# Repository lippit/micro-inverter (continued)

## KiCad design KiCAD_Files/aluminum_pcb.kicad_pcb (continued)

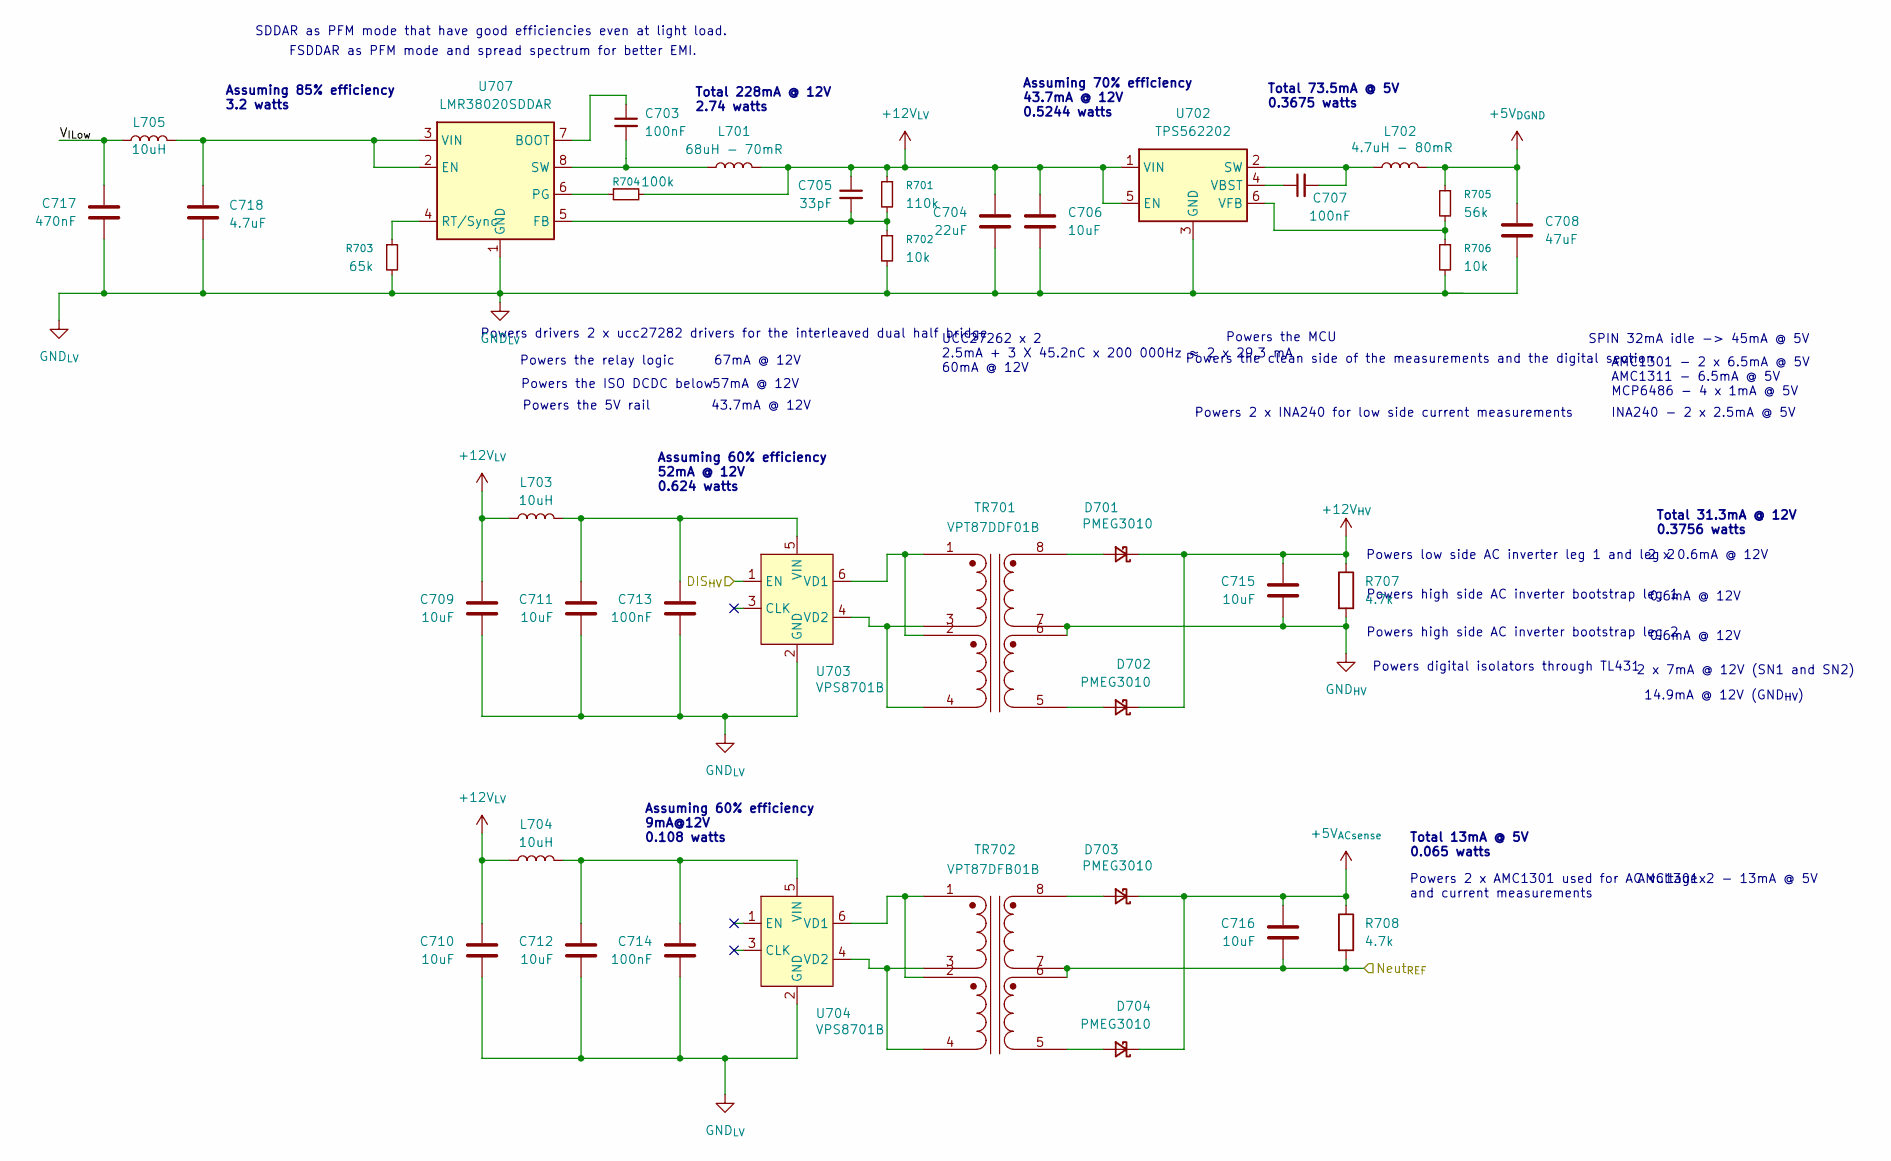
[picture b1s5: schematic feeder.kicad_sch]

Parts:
C703, C707: 100nF; C_0805_2012Metric
C704: 22uF; C_1210_3225Metric
C705: 33pF; C_0805_2012Metric
C706: 10uF; C_0805_2012Metric
C708: 47uF; C_1206_3216Metric
C709, C710, C711, C712, C715, C716: 10uF; C_0805_2012Metric; LCSC C440198
C713, C714: 100nF; C_0603_1608Metric; LCSC C14663
C717: 470nF; C_0805_2012Metric; Voltage_Rating 100V
C718: 4.7uF; C_1210_3225Metric; Voltage_Rating 100V
D701, D702, D703, D704: PMEG3010; D_SOD-323F; LCSC C255586
L701: 68uH - 70mR; L_12x12mm_H6mm; LCSC C7587712
L702: 4.7uH - 80mR; L_Cenker_CKCS4020; LCSC C3002596
L703, L704: 10uH; L_0805_2012Metric
L705: 10uH; L_1210_3225Metric
R701: 110k; R_0805_2012Metric
R702, R706: 10k; R_0805_2012Metric
R703: 65k; R_0805_2012Metric
R704: 100k; R_0805_2012Metric
R705: 56k; R_0805_2012Metric
R707, R708: 4.7k; R_0603_1608Metric; LCSC C23162
TR701: VPT87DDF01B; VPT87BB-01B; LCSC C2846916
TR702: VPT87DFB01B; VPT87BB-01B; LCSC C2846915
U702: TPS562202; SOT-563; LCSC C2877547
U703, U704: VPS8701B; SOT-23-6; LCSC C5189123
U707: LMR38020SDDAR; Texas_HSOP-8-1EP_3.9x4.9mm_P1.27mm_ThermalVias; LCSC C3192337

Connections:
+5V_{ACsense}: C716.1, D703.1 (K), D704.1 (K), R708.1; also elsewhere on the board
+5V_{DGND}: C708.1, L702.2, R705.1; also elsewhere on the board
+12V_{HV}: C715.1, D701.1 (K), D702.1 (K), R707.1; also elsewhere on the board
/Feeder/DIS_{HV}: U703.1 (EN); also elsewhere on the board
/Feeder/Neut_{REF}: C716.2, R708.2, TR702.6 (SB), TR702.7 (SA); also elsewhere on the board
/Feeder/V_{ILow}: C717.1, L705.1
GND_{HV}: C715.2, R707.2, TR701.6 (SB), TR701.7 (SA); also elsewhere on the board
unnamed: D701.2 (A), TR701.8 (SB)
unnamed: D702.2 (A), TR701.5 (SA)
unnamed: D703.2 (A), TR702.8 (SB)
unnamed: D704.2 (A), TR702.5 (SA)
unnamed: C707.2, L702.1, U702.2 (SW)
unnamed: C707.1, U702.4 (VBST)
unnamed: R705.2, R706.1, U702.6 (VFB)
unnamed: TR701.1 (AA), TR701.2 (AA), U703.6 (VD1)
unnamed: TR701.3 (AB), TR701.4 (AB), U703.4 (VD2)
unnamed: C711.1, C713.1, L703.2, U703.5 (VIN)
unnamed: TR702.1 (AA), TR702.2 (AA), U704.6 (VD1)
unnamed: TR702.3 (AB), TR702.4 (AB), U704.4 (VD2)
unnamed: C712.1, C714.1, L704.2, U704.5 (VIN)
unnamed: C703.1, U707.7 (BOOT)
unnamed: C718.1, L705.2, U707.2 (EN), U707.3 (VIN)
unnamed: C705.2, R701.2, R702.1, U707.5 (FB)
unnamed: R704.1, U707.6 (PG)
unnamed: R703.1, U707.4 (RT/Sync)
unnamed: C703.2, L701.1, U707.8 (SW)

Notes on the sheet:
Powers the 5V rail
Powers digital isolators through TL431
Total 73.5mA @ 5V 0.3675 watts
Assuming 70% efficiency 43.7mA @ 12V 0.5244 watts
AMC1301x2 - 13mA @ 5V
INA240 - 2 x 2.5mA @ 5V
Powers the clean side of the measurements and the digital section
Powers 2 x AMC1301 used for AC voltage and current measurements
Powers high side AC inverter bootstrap leg 1
Total 13mA @ 5V 0.065 watts
Assuming 60% efficiency 9mA@12V 0.108 watts
Assuming 60% efficiency 52mA @ 12V 0.624 watts
0.6mA @ 12V
Powers 2 x INA240 for low side current measurements
Powers low side AC inverter leg 1 and leg 2
Powers the ISO DCDC below
SPIN 32mA idle -> 45mA @ 5V
14.9mA @ 12V (GND_{HV})
Powers drivers 2 x ucc27282 drivers for the interleaved dual half bridge
57mA @ 12V
UCC27262 x 2 2.5mA + 3 X 45.2nC x 200 000Hz ≈ 2 x 29.3 mA 60mA @ 12V
FSDDAR as PFM mode and spread spectrum for better EMI.
43.7mA @ 12V
2 x 0.6mA @ 12V
AMC1301 - 2 x 6.5mA @ 5V AMC1311 - 6.5mA @ 5V MCP6486 - 4 x 1mA @ 5V
2 x 7mA @ 12V (SN1 and SN2)
Total 228mA @ 12V 2.74 watts
Powers the MCU
Assuming 85% efficiency 3.2 watts
Total 31.3mA @ 12V 0.3756 watts
Powers the relay logic
67mA @ 12V
Powers high side AC inverter bootstrap leg 2
SDDAR as PFM mode that have good efficiencies even at light load.

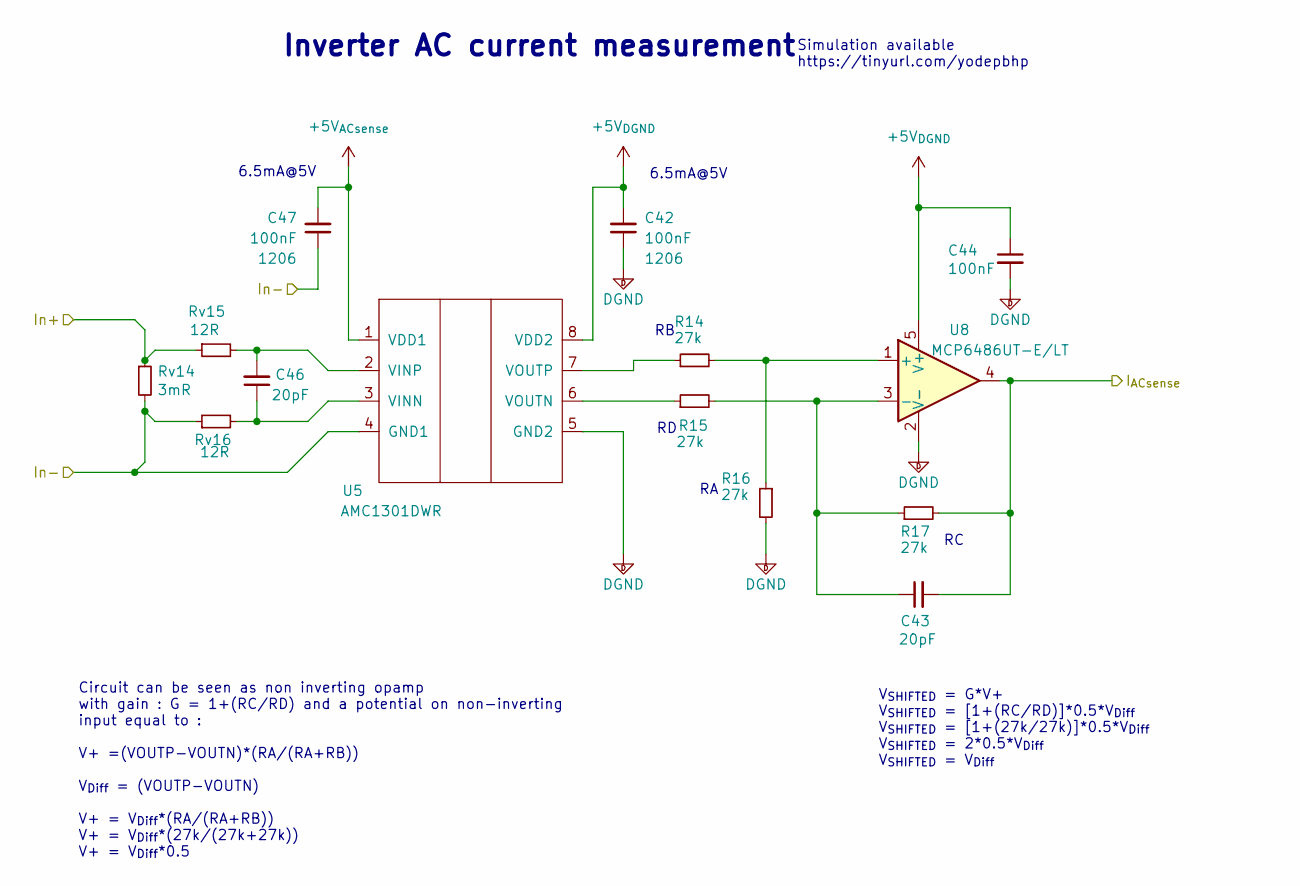
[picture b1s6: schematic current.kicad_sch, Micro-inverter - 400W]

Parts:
C42, C47: 100nF; C_1206_3216Metric; Voltage 50V; LCSC C5449000
C43, C46: 20pF; C_0805_2012Metric; Voltage 50V
C44: 100nF; C_0805_2012Metric; Voltage 50V; LCSC C5449000
R14, R15, R16, R17: 27k; R_0805_2012Metric
Rv14: 3mR; R_2512_6332Metric
Rv15, Rv16: 12R; R_0805_2012Metric
U5: AMC1301DWR; SOIC-8_7.5x5.85mm_P1.27mm; LCSC C190273
U8: MCP6486UT-E/LT; SOT-353_SC-70-5_Handsoldering; LCSC C5224800

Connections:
+5V_{ACsense}: C47.2, U5.1 (VDD1); also elsewhere on the board
+5V_{DGND}: C42.2, C44.1, U5.8 (VDD2), U8.5 (V+); also elsewhere on the board
/Feeder/Neut_{REF}: C47.1, Rv14.2, Rv16.1, U5.4 (GND1); also elsewhere on the board
/Microcontroller/I_{AC}: C43.2, R17.2, U8.4; also elsewhere on the board
/Power/AC Current sense/In+: Rv14.1, Rv15.1; also elsewhere on the board
unnamed: C46.1, Rv16.2, U5.3 (VINN)
unnamed: C46.2, Rv15.2, U5.2 (VINP)
unnamed: R15.1, U5.6 (VOUTN)
unnamed: R14.1, U5.7 (VOUTP)
unnamed: R14.2, R16.1, U8.1 (+)
unnamed: C43.1, R15.2, R17.1, U8.3 (-)

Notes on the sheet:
Simulation available https://tinyurl.com/yodepbhp
6.5mA@5V
Circuit can be seen as non inverting opamp with gain : G = 1+(RC/RD) and a potential on non-inverting input equal to : V+ =(VOUTP-VOUTN)*(RA/(RA+RB)) V_{Diff} = (VOUTP-VOUTN) V+ = V_{Diff}*(RA/(RA+RB)) V+ = V_{Diff}*(27k/(27k+27k)) V+ = V_{Diff}*0.5
V_{SHIFTED} = G*V+ V_{SHIFTED} = [1+(RC/RD)]*0.5*V_{Diff} V_{SHIFTED} = [1+(27k/27k)]*0.5*V_{Diff} V_{SHIFTED} = 2*0.5*V_{Diff} V_{SHIFTED} = V_{Diff}
Inverter AC current measurement

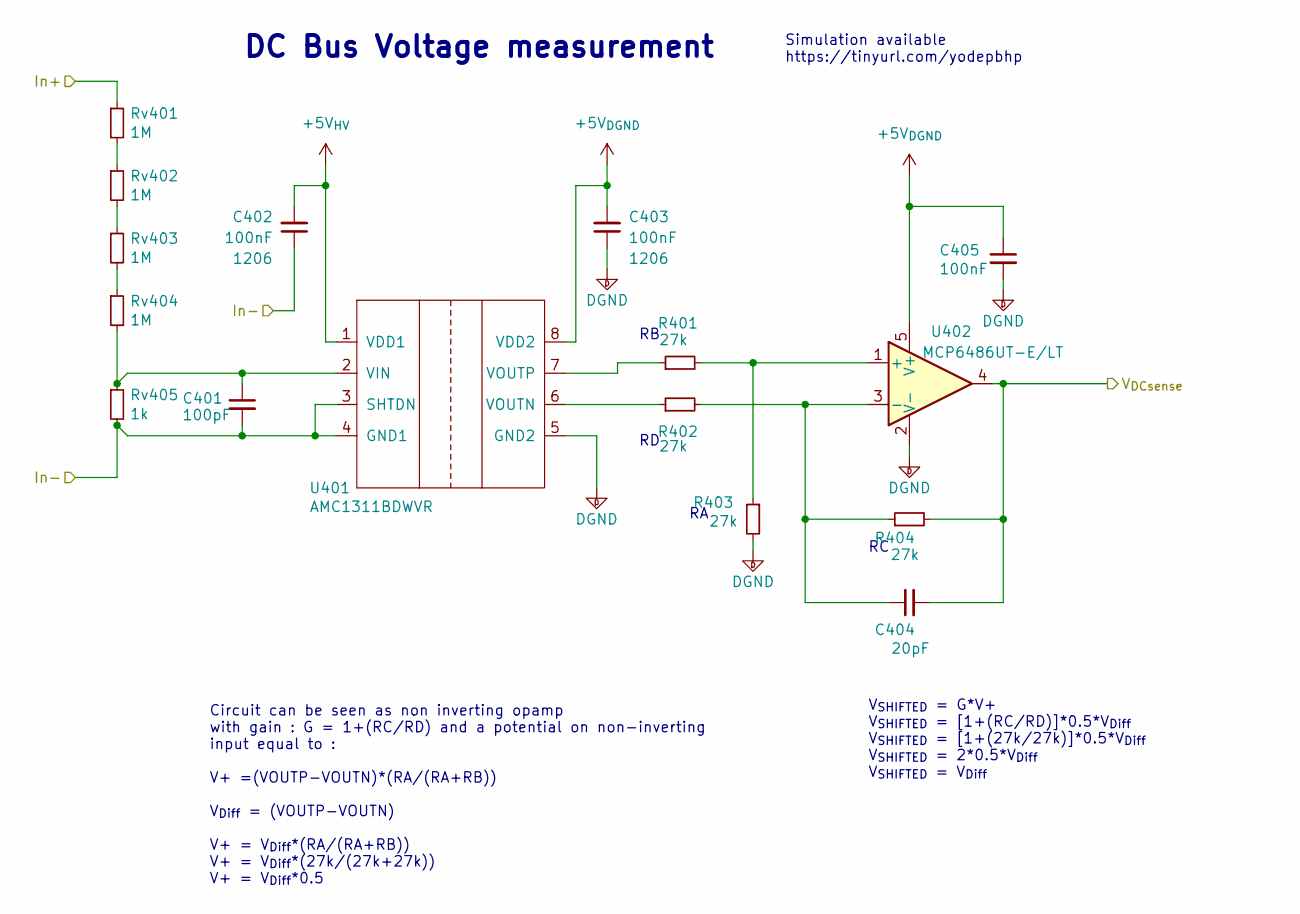
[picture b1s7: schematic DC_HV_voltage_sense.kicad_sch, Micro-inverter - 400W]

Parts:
C401: 100pF; C_0805_2012Metric; Voltage 50V
C402, C403: 100nF; C_1206_3216Metric; Voltage 50V; LCSC C5449000
C404: 20pF; C_0805_2012Metric; Voltage 50V
C405: 100nF; C_0805_2012Metric; Voltage 50V; LCSC C5449000
R401, R402, R403, R404: 27k; R_0805_2012Metric
Rv401, Rv402, Rv403, Rv404: 1M; R_0805_2012Metric
Rv405: 1k; R_0805_2012Metric
U401: AMC1311BDWVR; SOIC-8_7.5x5.85mm_P1.27mm; LCSC C783598
U402: MCP6486UT-E/LT; SOT-353_SC-70-5_Handsoldering; LCSC C5224800

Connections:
+5V_{DGND}: C403.2, C405.1, U401.8 (VDD2), U402.5 (V+); also elsewhere on the board
+5V_{HV}: C402.2, U401.1 (VDD1); also elsewhere on the board
/Microcontroller/V_{DCBus}: C404.2, R404.2, U402.4; also elsewhere on the board
/Power/HV_{BUS}: Rv401.1; also elsewhere on the board
GND_{HV}: C401.2, C402.1, Rv405.2, U401.3 (SHTDN), U401.4 (GND1); also elsewhere on the board
unnamed: Rv401.2, Rv402.1
unnamed: Rv402.2, Rv403.1
unnamed: Rv403.2, Rv404.1
unnamed: C401.1, Rv404.2, Rv405.1, U401.2 (VIN)
unnamed: R402.1, U401.6 (VOUTN)
unnamed: R401.1, U401.7 (VOUTP)
unnamed: R401.2, R403.1, U402.1 (+)
unnamed: C404.1, R402.2, R404.1, U402.3 (-)

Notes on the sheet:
Circuit can be seen as non inverting opamp with gain : G = 1+(RC/RD) and a potential on non-inverting input equal to : V+ =(VOUTP-VOUTN)*(RA/(RA+RB)) V_{Diff} = (VOUTP-VOUTN) V+ = V_{Diff}*(RA/(RA+RB)) V+ = V_{Diff}*(27k/(27k+27k)) V+ = V_{Diff}*0.5
DC Bus Voltage measurement
V_{SHIFTED} = G*V+ V_{SHIFTED} = [1+(RC/RD)]*0.5*V_{Diff} V_{SHIFTED} = [1+(27k/27k)]*0.5*V_{Diff} V_{SHIFTED} = 2*0.5*V_{Diff} V_{SHIFTED} = V_{Diff}
Simulation available https://tinyurl.com/yodepbhp

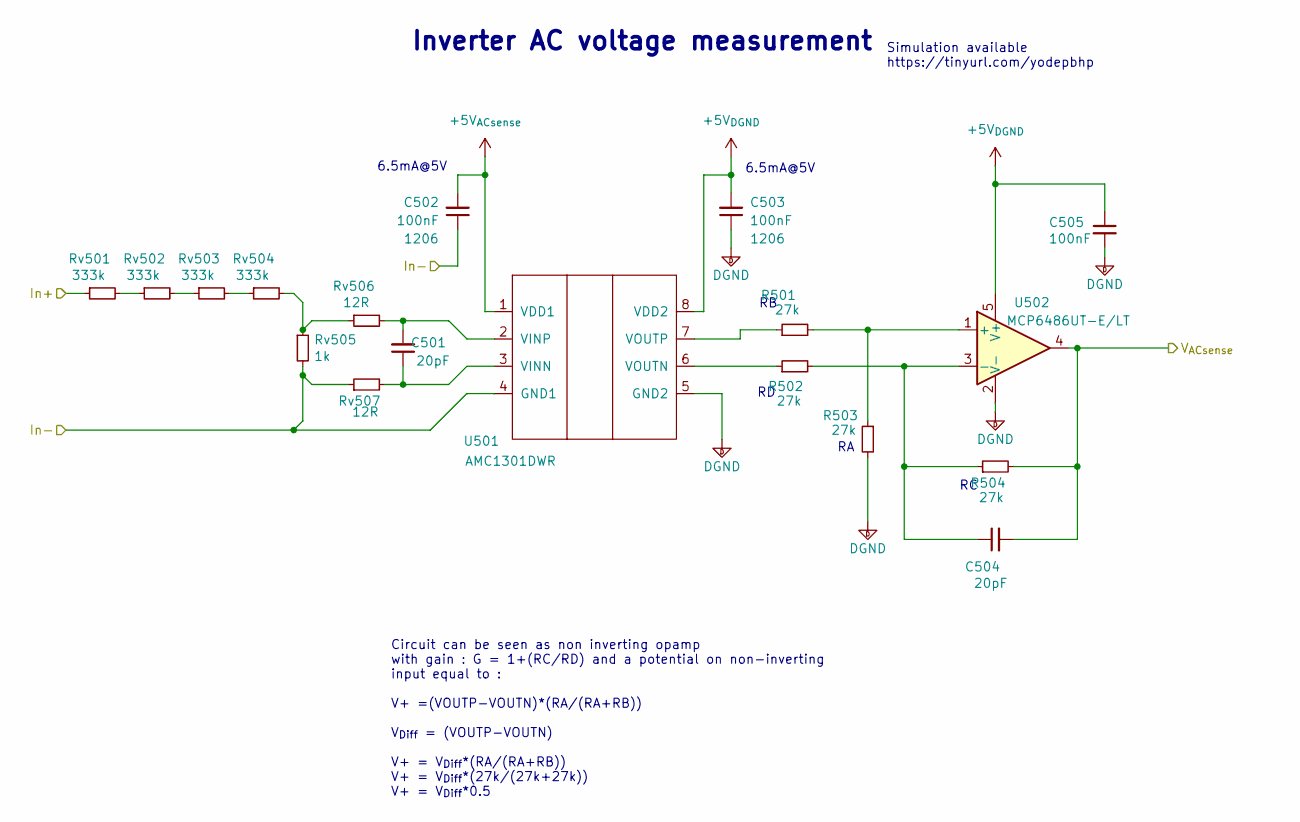
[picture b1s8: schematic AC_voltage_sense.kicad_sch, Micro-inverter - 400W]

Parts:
C501, C504: 20pF; C_0805_2012Metric; Voltage 50V
C502, C503: 100nF; C_1206_3216Metric; Voltage 50V; LCSC C5449000
C505: 100nF; C_0805_2012Metric; Voltage 50V; LCSC C5449000
R501, R502, R503, R504: 27k; R_0805_2012Metric
Rv501, Rv502, Rv503, Rv504: 333k; R_0805_2012Metric
Rv505: 1k; R_0805_2012Metric
Rv506, Rv507: 12R; R_0805_2012Metric
U501: AMC1301DWR; SOIC-8_7.5x5.85mm_P1.27mm; LCSC C190273
U502: MCP6486UT-E/LT; SOT-353_SC-70-5_Handsoldering; LCSC C5224800

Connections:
+5V_{ACsense}: C502.2, U501.1 (VDD1); also elsewhere on the board
+5V_{DGND}: C503.2, C505.1, U501.8 (VDD2), U502.5 (V+); also elsewhere on the board
/Feeder/Neut_{REF}: C502.1, Rv505.2, Rv507.1, U501.4 (GND1); also elsewhere on the board
/Microcontroller/V_{AC}: C504.2, R504.2, U502.4; also elsewhere on the board
/Power/Grid Voltage sense/In+: Rv501.1; also elsewhere on the board
unnamed: Rv501.2, Rv502.1
unnamed: Rv502.2, Rv503.1
unnamed: Rv503.2, Rv504.1
unnamed: Rv504.2, Rv505.1, Rv506.1
unnamed: C501.1, Rv507.2, U501.3 (VINN)
unnamed: C501.2, Rv506.2, U501.2 (VINP)
unnamed: R502.1, U501.6 (VOUTN)
unnamed: R501.1, U501.7 (VOUTP)
unnamed: R501.2, R503.1, U502.1 (+)
unnamed: C504.1, R502.2, R504.1, U502.3 (-)

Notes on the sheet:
Circuit can be seen as non inverting opamp with gain : G = 1+(RC/RD) and a potential on non-inverting input equal to : V+ =(VOUTP-VOUTN)*(RA/(RA+RB)) V_{Diff} = (VOUTP-VOUTN) V+ = V_{Diff}*(RA/(RA+RB)) V+ = V_{Diff}*(27k/(27k+27k)) V+ = V_{Diff}*0.5
Inverter AC voltage measurement
6.5mA@5V
Simulation available https://tinyurl.com/yodepbhp

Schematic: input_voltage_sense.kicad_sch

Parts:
C701: 1nF; C_0805_2012Metric
C702: 100nF; C_0805_2012Metric; Voltage 50V; LCSC C5449000
Rv701: 1M; R_0805_2012Metric
Rv702: 16K; R_0805_2012Metric
U701: MCP6486UT-E/LT; SOT-353_SC-70-5_Handsoldering; LCSC C5224800

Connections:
+5V_{DGND}: C702.1, U701.5 (V+); also elsewhere on the board
/Microcontroller/V_{ILow}: U701.3 (-), U701.4; also elsewhere on the board
/Power/V_{ILow}: Rv701.1; also elsewhere on the board
unnamed: C701.1, Rv701.2, Rv702.1, U701.1 (+)

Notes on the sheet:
DC input voltage measurement

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
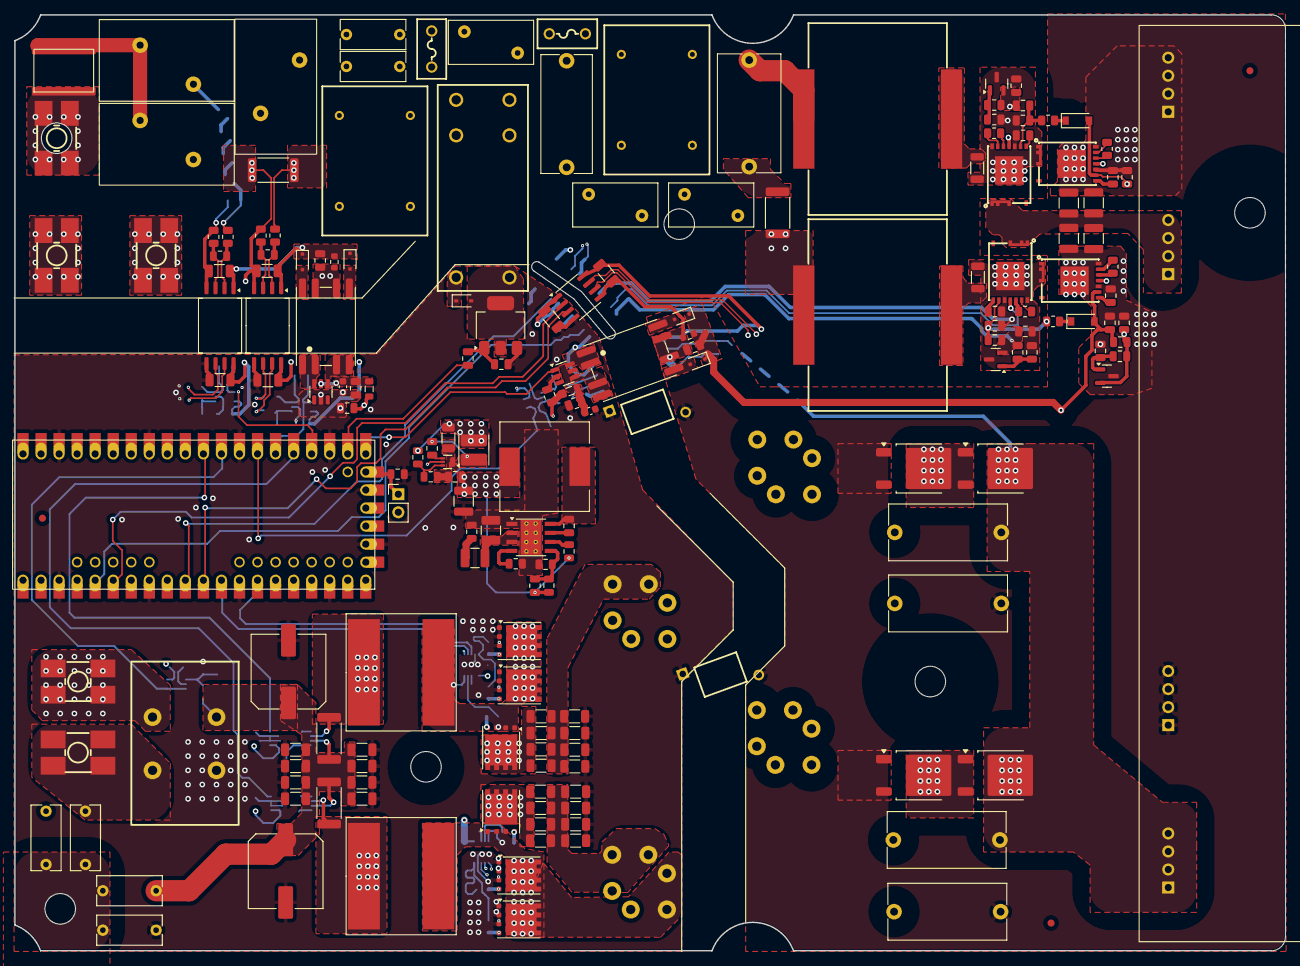
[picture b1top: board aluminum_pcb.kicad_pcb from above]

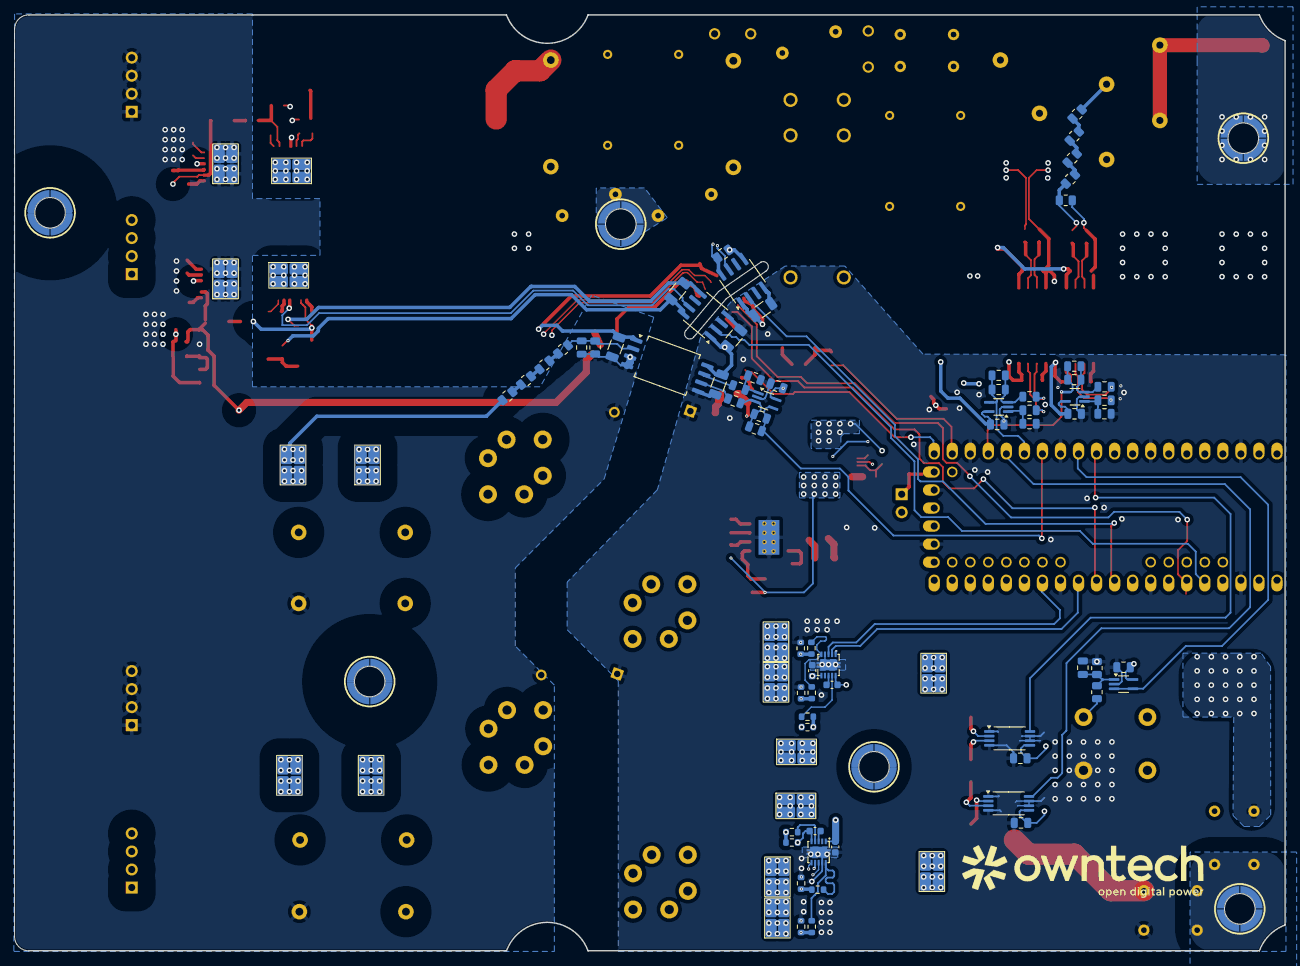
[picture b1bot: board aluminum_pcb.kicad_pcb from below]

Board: 4 copper layers, 178.9 x 131.8 mm, 277 parts (91 on the bottom side), 144 nets.

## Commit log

2025-07-16 Changed the architecture from DAB to full-bridge. Added low side feeder.
2026-01-13 Schematic close to completion.
2026-01-16 First routing pass complete.
2026-01-17 Added missing tracks for sensors and relay. Fixed many routing issues.
2026-01-19 Added DRC rules according to IEC60664 and IPC2221.
2026-01-19 Added PE keepouts. Adding thermal vias. DRC passing.
2026-01-19 Added HF X2 caps, Improved low side Y2 placement. Improved Silkscreen.
2026-01-23 Added passive references. Added ESD protection for MCU pins.
2026-01-23 Partially adressing #2.
2026-01-23 Added TL431 for AC measurement 5V regulation. Added more film capacitance. Increased size of 100V ceramic caps to 1210.
2026-01-27 V0.9 as ordered 23/01/26. Improved silkscreen, added 1nF on enable pin signals.
2026-01-27 Suppressing non relevant datasheets.
2026-01-27 Tidy up repo structure.
2026-01-27 Suppressing non relevant footprints and 3D files.
2026-01-27 Tidied up the schematic. Added the pdf version for V0.9.
2026-01-29 Added mechanical assets - cabling, cable glands, MC4 and AC connectors.
2026-01-30 Adding ngspice simulations for EMC. Adding schematic pdf.
2026-01-30 Added contribution section.
2026-01-30 Added safety section.
2026-01-30 Adding a specification table.
2026-01-30 Added team banneer.
2026-01-30 Adding Contribute.md
2026-01-31 First version of the overall code for the uVerter
2026-01-31 Updates the readme and the contribute to take into account stuff to be done on the firmware
2026-02-03 Modified the differential inductor filter footprints slightly. Solves #2.
2026-02-03 Added LSW3 and LSW4 netclass (Fix #3). Tidied up courtyard DRC for testpoints.
2026-02-04 Add CMSIS_DSP_FASTMATH to Zephyr project config
    Required to use the functions arm_sin_f32 and arm_cos_f32
2026-02-04 Add .gitignore to ignore .pio subdirectory
    This directory is automatically created when compiling with PlatformIO.
2026-02-04 Add compile instructions to README
2026-02-06 Enhancing standards section according to #1
2026-02-06 Refined spec according to #6
